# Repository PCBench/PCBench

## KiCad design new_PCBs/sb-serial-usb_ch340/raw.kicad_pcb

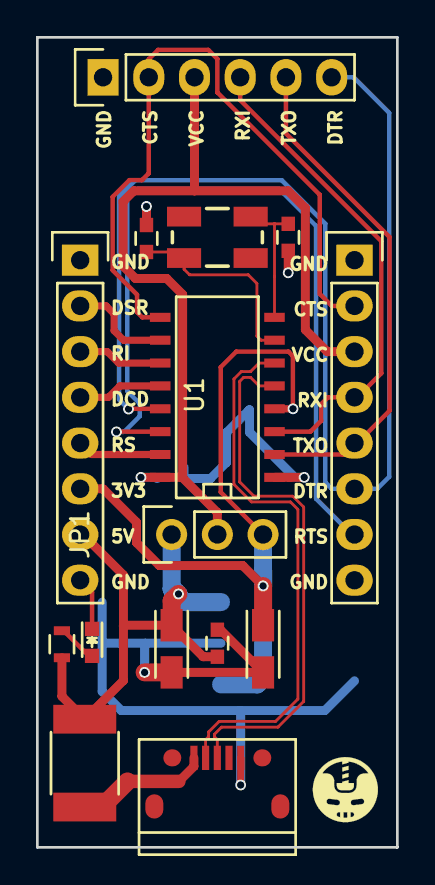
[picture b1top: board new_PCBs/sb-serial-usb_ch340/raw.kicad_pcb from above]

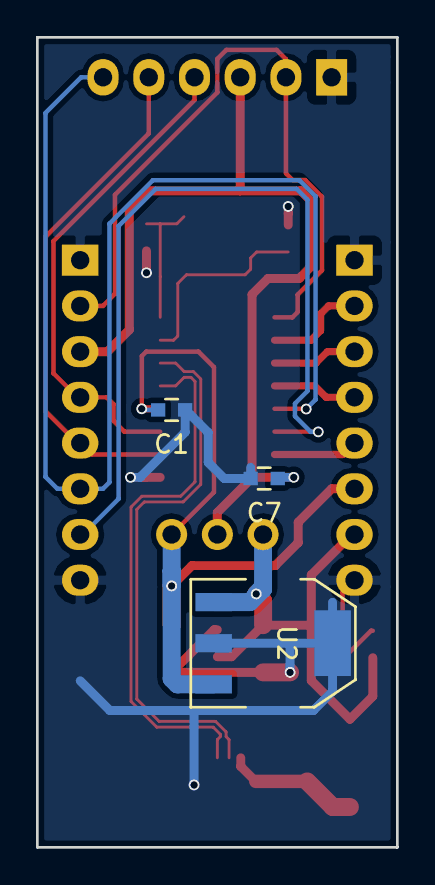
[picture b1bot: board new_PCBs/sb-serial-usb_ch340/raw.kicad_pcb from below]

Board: 2 copper layers, 20.0 x 45.0 mm, 18 parts (3 on the bottom side), 19 nets.

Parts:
C1: 10n; C_0603
C2, C3: 22p; C_0603
C4, C6: 10u 6V TANT; TantalC_SizeA_EIA-3216_Reflow
C5: 1u; C_0603
C7: 100n; C_0603
D1: BLUE; LED_0603
F1: 1.5A; R_1812
JP1: JUMPER3; Pin_Header_Straight_1x03
P1: CONN_01X06; Pin_Header_Straight_1x06
P2, P3: CONN_01X08; Pin_Header_Straight_1x08
P4: MINI-USB; USB_Micro-B
R1: 1K; R_0603
U1: CH340G; SO-16-N
U2: LDO MIC39100 3.3V; SOT-223
Y1: 12Mhz; CRYSTAL-SMD-5X3

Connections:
+5V: C4.1, C5.1, F1.2, JP1.1, P3.7, R1.2, U2.1
CTS: P1.2, P2.2, U1.9
D+: P4.3, U1.5
D-: P4.2, U1.6
DCD: P3.4, U1.12
DSR: P3.2, U1.10
DTR: P1.6, P2.6, U1.13
GND: C1.1, C2.2, C3.2, C4.2, C5.2, C6.2, C7.2, D1.1, P1.1, P2.1, P2.8, P3.1, P3.8, P4.5, U1.1, U2.2, U2.4
unnamed: C2.1, U1.7, Y1.1
unnamed: C3.1, U1.8, Y1.2
unnamed: D1.2, R1.1
unnamed: F1.1, P4.1
RI: P3.3, U1.11
RS232: P3.5, U1.15
RTS: P2.7, U1.14
RXI: P1.4, P2.4, U1.3
TXO: P1.5, P2.5, U1.2
V3: C1.2, C6.1, JP1.3, P3.6, U1.4, U2.3
VCC: C7.1, JP1.2, P1.3, P2.3, U1.16

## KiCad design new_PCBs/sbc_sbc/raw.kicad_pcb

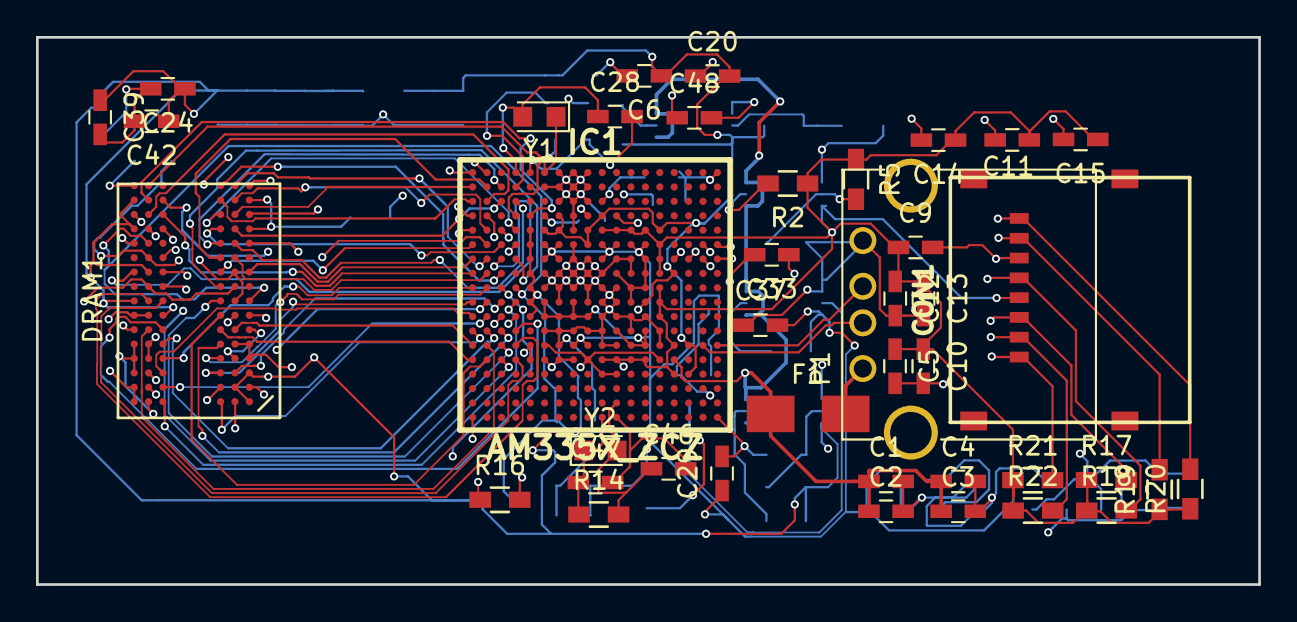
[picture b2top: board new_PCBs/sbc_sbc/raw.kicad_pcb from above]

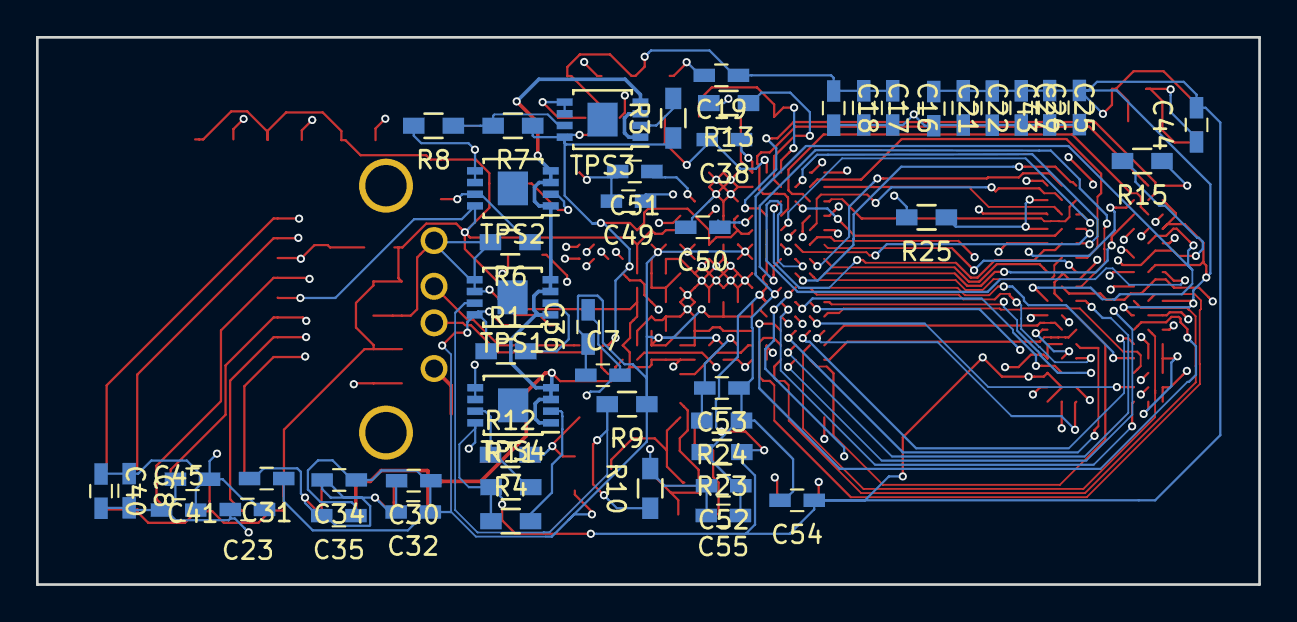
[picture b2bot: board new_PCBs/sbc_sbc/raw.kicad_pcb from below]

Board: 4 copper layers, 67.9 x 30.4 mm, 91 parts (50 on the bottom side), 85 nets.

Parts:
C1, C2, C3, C4, C15, C20, C26, C27, C37, C44, C45: 10uF; C_0603_HandSoldering
C5, C6, C7, C8: 22uF; C_0603_HandSoldering
C9, C10, C11, C12, C13, C14, C16, C17, C18, C19, C29, C30, C31, C32, C33, C34, C35, C36: 10nF; C_0603_HandSoldering
C21, C22, C23, C24, C25, C39, C40, C41, C42, C43, C48, C49, C50, C51: 1uF; C_0603_HandSoldering
C28, C38: 25pF; C_0603_HandSoldering
C46, C47: 24pF; C_0603_HandSoldering
C52, C53, C54, C55: 0.1uF; C_0603_HandSoldering
CON1: Micro_SD_Card; MICRO_SD_HINGE_AMP
DRAM1: DRAM-IS43TR16128B-125KBL; BGA-96_pitch0.8mm_dia0.4mm
F1: Polyfuse; Fuse_SMD1206_HandSoldering
IC1: AM335X_ZCZ; bga-csg324
P1: USB_A
R1, R2, R3, R4: 499K; R_0603_HandSoldering
R5: 250K; R_0603_HandSoldering
R6, R8, R10, R12: 80K; R_0603_HandSoldering
R7: 100K; R_0603_HandSoldering
R9: 30K; R_0603_HandSoldering
R11: 70K; R_0603_HandSoldering
R13, R17, R18, R19, R20, R21, R22, R25: 10K; R_0603_HandSoldering
R14: 1M; R_0603_HandSoldering
R15: 240; R_0603_HandSoldering
R16: 49.9; R_0603_HandSoldering
R23, R24: 1K; R_0603_HandSoldering
TPS1, TPS2, TPS3, TPS4: TPS82084; MSOP-8-1EP_3x3mm_Pitch0.65mm
Y1: 32.768KHz; Crystal_SMD_2012-2pin_2.0x1.2mm_HandSoldering
Y2: 24MHz; Crystal_SMD_2012-2pin_2.0x1.2mm_HandSoldering

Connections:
1.1V: C7.1, C29.1, C30.1, C31.1, C32.1, C33.1, C34.1, C35.1, C36.1, C37.2, IC1.A2, IC1.F6, IC1.F7, IC1.F10, IC1.F11, IC1.F12, IC1.F13, IC1.G6, IC1.G7, IC1.G10, IC1.G13, IC1.H11, IC1.H13, IC1.J12, IC1.J13, IC1.K6, IC1.K8, IC1.K12, IC1.L6, IC1.L7, IC1.L8, IC1.L9, IC1.M11, IC1.M13, IC1.N8, IC1.N9, IC1.N12, IC1.N13, R1.1, R9.1, TPS1.8
1.8V: C6.1, C16.1, C17.1, C18.1, C19.1, C20.2, IC1.D7, IC1.D10, IC1.E6, IC1.E7, IC1.E9, IC1.E14, IC1.F9, IC1.H15, IC1.K13, IC1.N6, IC1.N16, IC1.P9, IC1.P14, IC1.R10, IC1.R11, IC1.R16, R3.1, R7.1, TPS3.8
+1.5V: C8.1, C21.1, C22.1, C23.1, C24.1, C25.1, C26.1, C27.2, C39.1, C40.1, C41.1, C42.1, C43.1, C44.2, C45.2, C54.1, DRAM1.A1, DRAM1.A8, DRAM1.B2, DRAM1.C1, DRAM1.C9, DRAM1.D2, DRAM1.D9, DRAM1.E9, DRAM1.F1, DRAM1.G7, DRAM1.H2, DRAM1.H9, DRAM1.K2, DRAM1.K8, DRAM1.N1, DRAM1.N9, DRAM1.R1, DRAM1.R9, IC1.E5, IC1.F5, IC1.G5, IC1.H5, IC1.J5, IC1.K5, IC1.L5, R4.1, R11.1, R23.1, R25.1, TPS4.8
+3V3: C5.1, C9.1, C10.1, C11.1, C12.1, C13.1, C14.1, C15.1, CON1.4, IC1.E10, IC1.E11, IC1.E12, IC1.E13, IC1.F14, IC1.G14, IC1.H14, IC1.J14, IC1.K14, IC1.L14, IC1.N5, IC1.N15, IC1.P5, IC1.P6, IC1.P7, IC1.P8, IC1.P10, IC1.P11, IC1.P12, IC1.P13, IC1.R15, R2.1, R5.1, R17.1, R18.1, R19.1, R20.1, R21.1, R22.1, TPS2.8
+5V: C1.1, C2.1, C3.1, C4.1, F1.1, IC1.P15, TPS1.1, TPS1.3, TPS1.4, TPS2.1, TPS2.3, TPS2.4, TPS3.1, TPS3.3, TPS3.4, TPS4.1, TPS4.3, TPS4.4
/1.1FB: R9.2, R10.1, TPS1.7
/1.5FB: R11.2, R12.1, TPS4.7
/1.8FB: R7.2, R8.1, TPS3.7
/3.3FB: R5.2, R6.1, TPS2.7
/DDR_A0: DRAM1.N3, IC1.F3
/DDR_A1: DRAM1.P7, IC1.H1
/DDR_A2: DRAM1.P3, IC1.E4
/DDR_A3: DRAM1.N2, IC1.C3
/DDR_A4: DRAM1.P8, IC1.C2
/DDR_A5: DRAM1.P2, IC1.B1
/DDR_A6: DRAM1.R8, IC1.D5
/DDR_A7: DRAM1.R2, IC1.E2
/DDR_A8: DRAM1.T8, IC1.D4
/DDR_A9: DRAM1.R3, IC1.C1
/DDR_A10: DRAM1.L7, IC1.F4
/DDR_A11: DRAM1.R7, IC1.F2
/DDR_A12: DRAM1.N7, IC1.E3
/DDR_A13: DRAM1.T3, IC1.H3
/DDR_BA0: DRAM1.M2, IC1.C4
/DDR_BA1: DRAM1.N8, IC1.E1
/DDR_BA2: DRAM1.M3, IC1.B3
/DDR_CASn: DRAM1.K3, IC1.F1
/DDR_CK: DRAM1.J7, IC1.D2
/DDR_CKE: DRAM1.K9, IC1.G3
/DDR_CKn: DRAM1.K7, IC1.D1
/DDR_CSn0: DRAM1.L2, IC1.H2
/DDR_D0: DRAM1.E3, IC1.M3
/DDR_D1: DRAM1.F7, IC1.M4
/DDR_D2: DRAM1.F2, IC1.N1
/DDR_D3: DRAM1.F8, IC1.N2
/DDR_D4: DRAM1.H3, IC1.N3
/DDR_D5: DRAM1.H8, IC1.N4
/DDR_D6: DRAM1.G2, IC1.P3
/DDR_D7: DRAM1.H7, IC1.P4
/DDR_D8: DRAM1.D7, IC1.J1
/DDR_D9: DRAM1.C3, IC1.K1
/DDR_D10: DRAM1.C8, IC1.K2
/DDR_D11: DRAM1.C2, IC1.K3
/DDR_D12: DRAM1.A7, IC1.K4
/DDR_D13: DRAM1.A2, IC1.L3
/DDR_D14: DRAM1.B8, IC1.L4
/DDR_D15: DRAM1.A3, IC1.M1
/DDR_DQM0: DRAM1.E7, IC1.M2
/DDR_DQM1: DRAM1.D3, IC1.J2
/DDR_DQS0: DRAM1.F3, IC1.P1
/DDR_DQS1: DRAM1.C7, IC1.L1
/DDR_DQSn0: DRAM1.G3, IC1.P2
/DDR_DQSn1: DRAM1.B7, IC1.L2
/DDR_ODT: DRAM1.K1, IC1.G1
/DDR_RASn: DRAM1.J3, IC1.G4
/DDR_RESETn: DRAM1.T2, IC1.G2, R25.2
/DDR_VREF: C52.1, C53.1, C54.2, C55.1, DRAM1.H1, DRAM1.M8, IC1.J4, R23.2, R24.1
/DDR_WEn: DRAM1.L3, IC1.B2
/DDR_ZQ: DRAM1.L8, R15.2
/MMC0_CLK: CON1.5, IC1.G17, R18.2
/MMC0_CMD: CON1.3, IC1.G18, R17.2
/MMC0_DAT0: CON1.7, IC1.G16, R19.2
/MMC0_DAT1: CON1.8, IC1.G15, R20.2
/MMC0_DAT2: CON1.1, IC1.F18, R21.2
/MMC0_DAT3: CON1.2, IC1.F17, R22.2
/USBD+: IC1.N17, P1.2
/USBD-: IC1.N18, P1.3
GND: C1.2, C2.2, C3.2, C4.2, C5.2, C6.2, C7.2, C8.2, C9.2, C10.2, C11.2, C12.2, C13.2, C14.2, C15.2, C16.2, C17.2, C18.2, C19.2, C20.1, C21.2, C22.2, C23.2, C24.2, C25.2, C26.2, C27.1, C29.2, C30.2, C31.2, C32.2, C33.2, C34.2, C35.2, C36.2, C37.1, C39.2, C40.2, C41.2, C42.2, C43.2, C44.1, C45.1, C48.2, C49.2, C50.2, C51.2, C52.2, C53.2, C55.2, CON1.6, DRAM1.A9, DRAM1.B1, DRAM1.B3, DRAM1.B9, DRAM1.D1, DRAM1.D8, DRAM1.E1, DRAM1.E2, DRAM1.E8, DRAM1.F9, DRAM1.G1, DRAM1.G8, DRAM1.G9, DRAM1.J2, DRAM1.J8, DRAM1.M1, DRAM1.M9, DRAM1.P1, DRAM1.P9, DRAM1.T1, DRAM1.T9, IC1.A1, IC1.A7, IC1.A8, IC1.A9, IC1.A18, IC1.B6, IC1.B7, IC1.B8, IC1.B9, IC1.C7, IC1.C8, IC1.C9, IC1.D8, IC1.E8, IC1.F8, IC1.G8, IC1.G9, IC1.G11, IC1.G12, IC1.H6, IC1.H7, IC1.H8, IC1.H9, IC1.H10, IC1.H12, IC1.J6, IC1.J7, IC1.J8, IC1.J9, IC1.J10, IC1.J11, IC1.K7, IC1.K9, IC1.K10, IC1.K11, IC1.L10, IC1.L11, IC1.L12, IC1.L13, IC1.M6, IC1.M7, IC1.M8, IC1.M9, IC1.M10, IC1.M12, IC1.M14, IC1.N7, IC1.N10, IC1.N11, IC1.N14, IC1.V1, IC1.V18, P1.4, R6.2, R8.2, R10.2, R12.2, R13.2, R15.1, R16.2, R24.2, TPS1.5, TPS1.6, TPS2.5, TPS2.6, TPS3.5, TPS3.6, TPS4.5, TPS4.6
GND_OSC0: C46.2, C47.2, IC1.V11
GND_OSC1: C28.2, C38.2, IC1.A5
unnamed: C28.1, IC1.A4, Y1.2
unnamed: C38.1, IC1.A6, Y1.1
unnamed: C46.1, IC1.U11, R14.2, Y2.2
unnamed: C47.1, IC1.V10, R14.1, Y2.1
unnamed: C48.1, IC1.D11
unnamed: C49.1, IC1.D9
unnamed: C50.1, IC1.D6
unnamed: C51.1, IC1.C10
unnamed: F1.2, P1.1
unnamed: IC1.B4, R13.1
unnamed: IC1.J3, R16.1
unnamed: R1.2, TPS1.2
unnamed: R2.2, TPS2.2
unnamed: R3.2, TPS3.2
unnamed: R4.2, TPS4.2

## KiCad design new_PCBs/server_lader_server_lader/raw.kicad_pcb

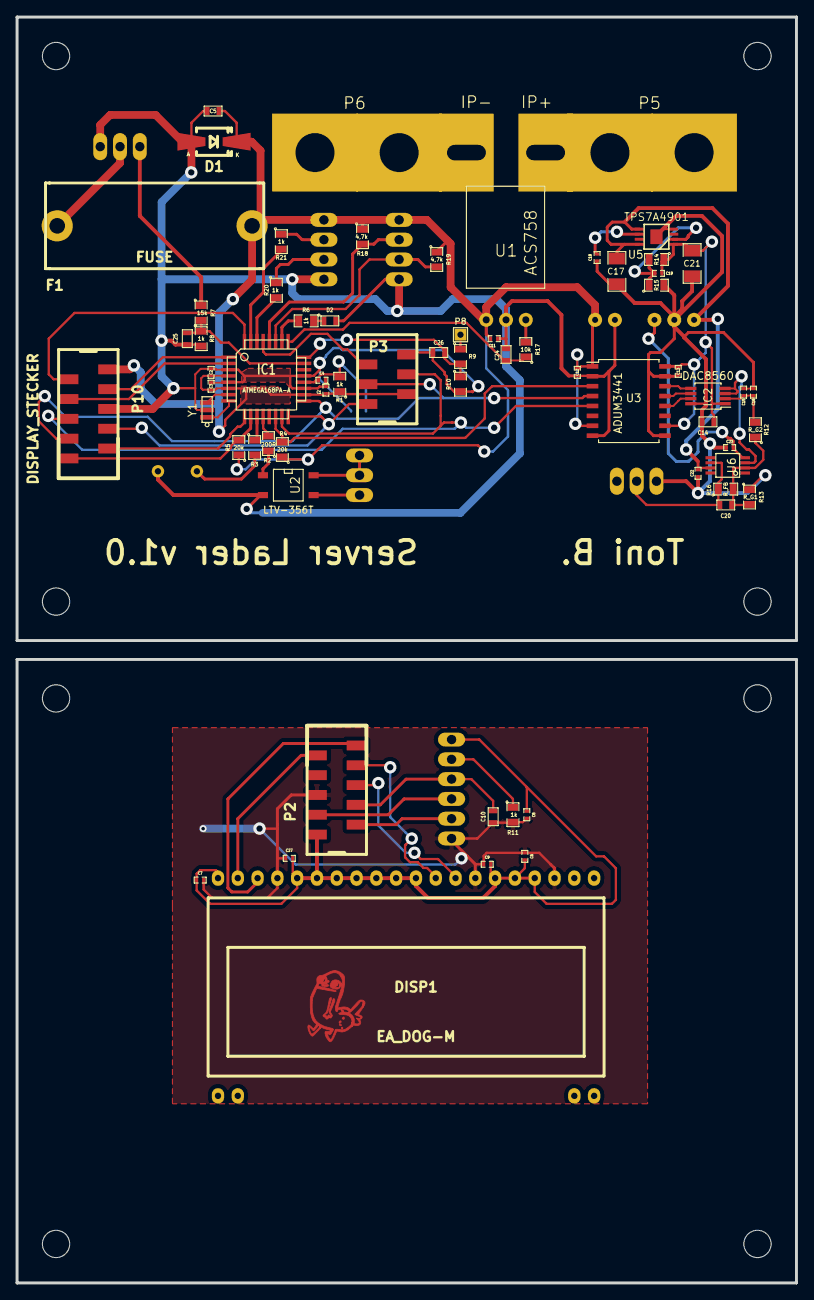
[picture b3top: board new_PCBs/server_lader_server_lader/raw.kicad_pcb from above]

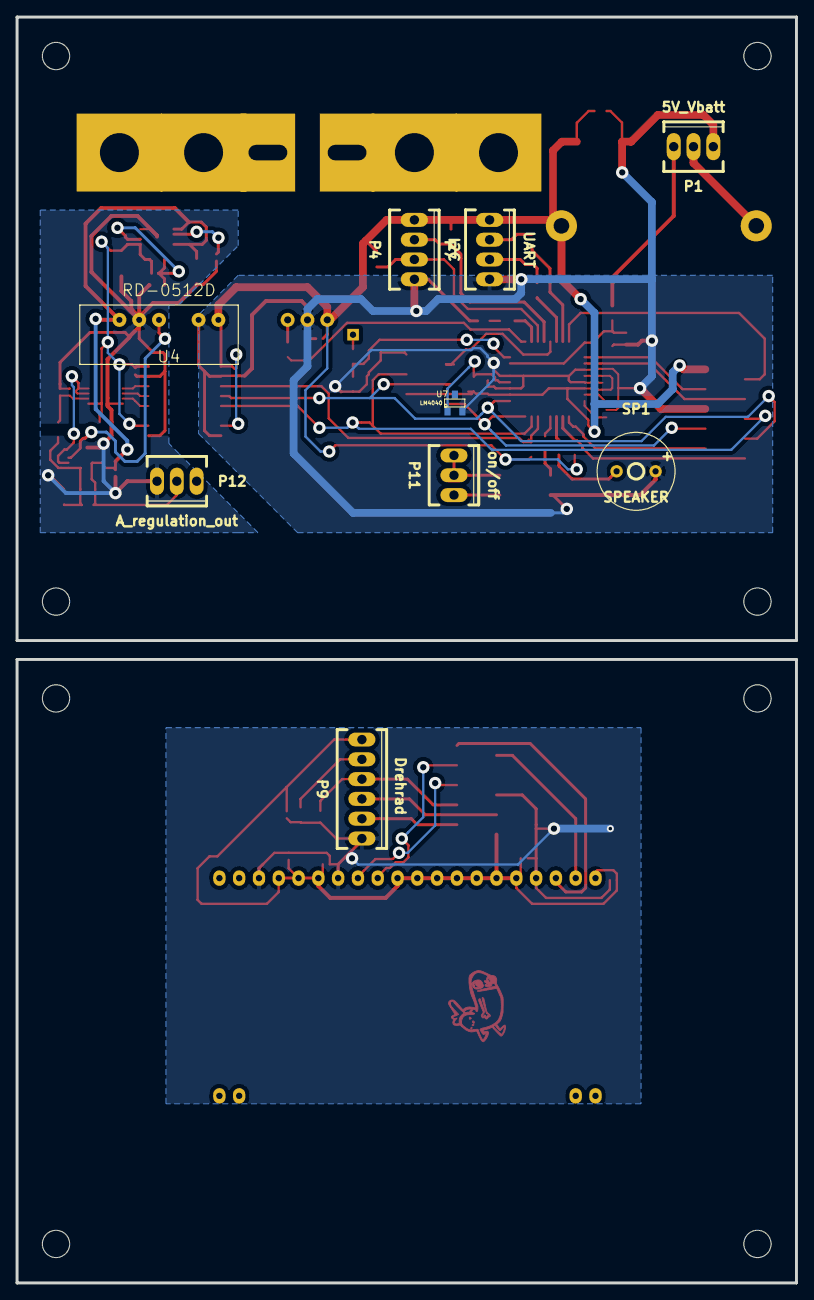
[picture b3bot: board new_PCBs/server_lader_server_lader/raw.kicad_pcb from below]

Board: 2 copper layers, 100.0 x 162.4 mm, 77 parts (9 on the bottom side), 59 nets.

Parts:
C1, C2, C3, C4, C6, C7, C8, C9, C11, C12, C13, C15, C16, C22, C23, C27: 100nF; SMD-0402
C5, C10, C14, C24: 1uF; SMD-0603
C17, C21: 10uF; SMD-1206
C18, C19: 10nF; SMD-0402
C20: C_comp; SMD-0603
C25: 100nF; SMD-0603
C26: C; SMD-0603
D1: ZENER 5,6V; Diode-Universal-SMA-SMB_Handsoldering
D2: LED; SMD-0603
DISP1: EA_DOG-M; EA_DOG-M_DISP
F1: FUSE; fuse_holder_Schurther
IC1: ATMEGA168PA-A; TQFP-32
IC2: DAC8560; MSOP-8_3x3mm_Pitch0.65mm
Outl: EuroBoard_halb_Type-I_100mmX80mm_holes
Outl#2: EuroBoard_halb_Type-I_100mmX80mm_holes
P1: 5V_Vbatt; Socket_MOLEX-KK-RM2-54mm_Lock_3pin_straight
P2, P10: DISPLAY_STECKER; micro_match5x2
P3: CONN_02X03; micro_match3x2
P4: I2C; Socket_MOLEX-KK-RM2-54mm_Lock_4pin_straight
P5: IP+; power_terminal
P6: IP-; power_terminal
P7: UART; Socket_MOLEX-KK-RM2-54mm_Lock_4pin_straight
P8: CONN_01X01; SIL-1
P9: Drehrad; Socket_MOLEX-KK-RM2-54mm_Lock_6pin_straight
P11: on/off; Socket_MOLEX-KK-RM2-54mm_Lock_3pin_straight
P12: A_regulation_out; Socket_MOLEX-KK-RM2-54mm_Lock_3pin_straight
R1, R6, R8, R11, R20, R21: 1k; SMD-0805
R2: 200R; SMD-0805
R3, R9, R10: R; SMD-0805
R4, R5: 20k; SMD-0805
R7: 15k; SMD-0805
R12: R_G2; SMD-0805
R13: R_G1; SMD-0805
R14: 33k; SMD-0805
R15, R17: 10k; SMD-0805
R16: R_FB; SMD-0805
R18, R19: 4,7k; SMD-0805
SP1: SPEAKER; Buzzer_AI-1027-TWT-5V-R
U1: ACS758; ACS758_PFF
U2: LTV-356T; SO-4
U3: ADUM3441; SOIC-16_7.5x10.3mm_Pitch1.27mm
U4: RD-0512D; RD-xx12D
U5: TPS7A4901; MSOP-8_power_pad
U6: OPA827; SSOP-8
U7: LM4040; SOT-23
Y1: RESONATEUR; CerOsc_3,2x1,3

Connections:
+5VA: C13.1, C14.1, C19.1, C21.1, IC2.1, R14.1, U3.10, U3.16, U5.1
+12V: C17.1, C22.1, U4.6, U5.5, U5.8, U6.7
-12V: C23.2, U4.4, U6.4
/A: IC1.32, P10.2
/A_D: P2.2, P9.2
/B: IC1.1, P10.3
/B_D: P2.3, P9.3
/CSB: IC1.10, P10.10, R5.2
/CSB_D: DISP1.38, P2.10
/MISO: IC1.16, P3.1, P10.7
/MOSI: IC1.15, P3.4, P10.6, U3.5
/MOSI_D: DISP1.28, P2.6
/RS: IC1.9, P10.9
/RST: IC1.29, P3.5
/RS_D: DISP1.39, P2.9
/S: IC1.2, P10.4
/SCK: IC1.17, P3.3, P10.8, U3.4
/SCK_D: DISP1.29, P2.8
/SCL: IC1.28, P4.3, R18.2
/SDA: IC1.27, P4.2, R19.2
/SS_DAC: IC1.14, R4.2, U3.3
/S_D: C10.1, P2.4, P9.4
/U_Netzteil: C25.1, IC1.23, R7.2, R8.1
/U_Strom: C24.1, IC1.25, R17.1
/U_reserve: C26.1, IC1.24, R9.2, R10.1
/V_current: C20.1, P12.2, R16.1, U6.6
/Vref: C15.1, C16.1, IC2.2, R12.2
/on: R2.1, U2.1
AGND: C13.2, C14.2, C15.2, C16.2, C17.2, C18.2, C21.2, C22.2, C23.1, IC2.8, P12.1, R13.1, R15.2, U3.9, U3.15, U4.5, U5.4, U5.9
GND: C1.2, C2.2, C3.2, C4.2, C5.2, C6.2, C7.2, C8.2, C9.2, C10.2, C11.2, C12.2, C24.2, C25.2, C26.2, C27.2, D1.1, D2.2, DISP1.23, DISP1.27, DISP1.37, IC1.3, IC1.5, IC1.19, IC1.21, P1.1, P2.5, P3.6, P4.1, P7.1, P9.1, P10.5, R8.2, R10.2, R11.2, SP1.2, U1.2, U2.2, U3.2, U3.8, U4.2, U7.2, Y1.2
unnamed: C4.1, IC1.20, R1.2, U7.1
unnamed: C18.1, U5.6
unnamed: C19.2, R14.2, R15.1, U5.2
unnamed: C20.2, R12.1, R13.2, R16.2, U6.2
unnamed: D2.1, R6.1
unnamed: F1.1, P1.2
unnamed: IC1.7, Y1.3
unnamed: IC1.8, Y1.1
unnamed: IC1.11, R3.1
unnamed: IC1.12, R2.2
unnamed: IC1.26, R6.2
unnamed: IC1.30, R20.2
unnamed: IC1.31, R21.2
unnamed: IC2.3, IC2.4, U6.3
unnamed: IC2.5, U3.14
unnamed: IC2.6, U3.13
unnamed: IC2.7, U3.12
unnamed: P1.3, R7.1
unnamed: P5.1, U1.4
unnamed: P6.1, U1.5
unnamed: P7.2, R20.1
unnamed: P7.3, R21.1
unnamed: P8.1, R9.1
unnamed: P9.5, R11.1
unnamed: P11.1, U2.3
unnamed: P11.2, P11.3, U2.4
unnamed: R3.2, SP1.1
unnamed: R17.2, U1.3
VCC: C1.1, C2.1, C3.1, C5.1, C6.1, C7.1, C8.1, C9.1, C11.1, C12.1, C27.1, D1.2, DISP1.24, DISP1.25, DISP1.26, DISP1.30, DISP1.31, DISP1.32, DISP1.33, DISP1.34, DISP1.35, DISP1.36, DISP1.40, F1.2, IC1.4, IC1.6, IC1.18, P2.1, P3.2, P4.4, P7.4, P9.6, P10.1, R1.1, R4.1, R5.1, R18.1, R19.1, U1.1, U3.1, U3.7, U4.1

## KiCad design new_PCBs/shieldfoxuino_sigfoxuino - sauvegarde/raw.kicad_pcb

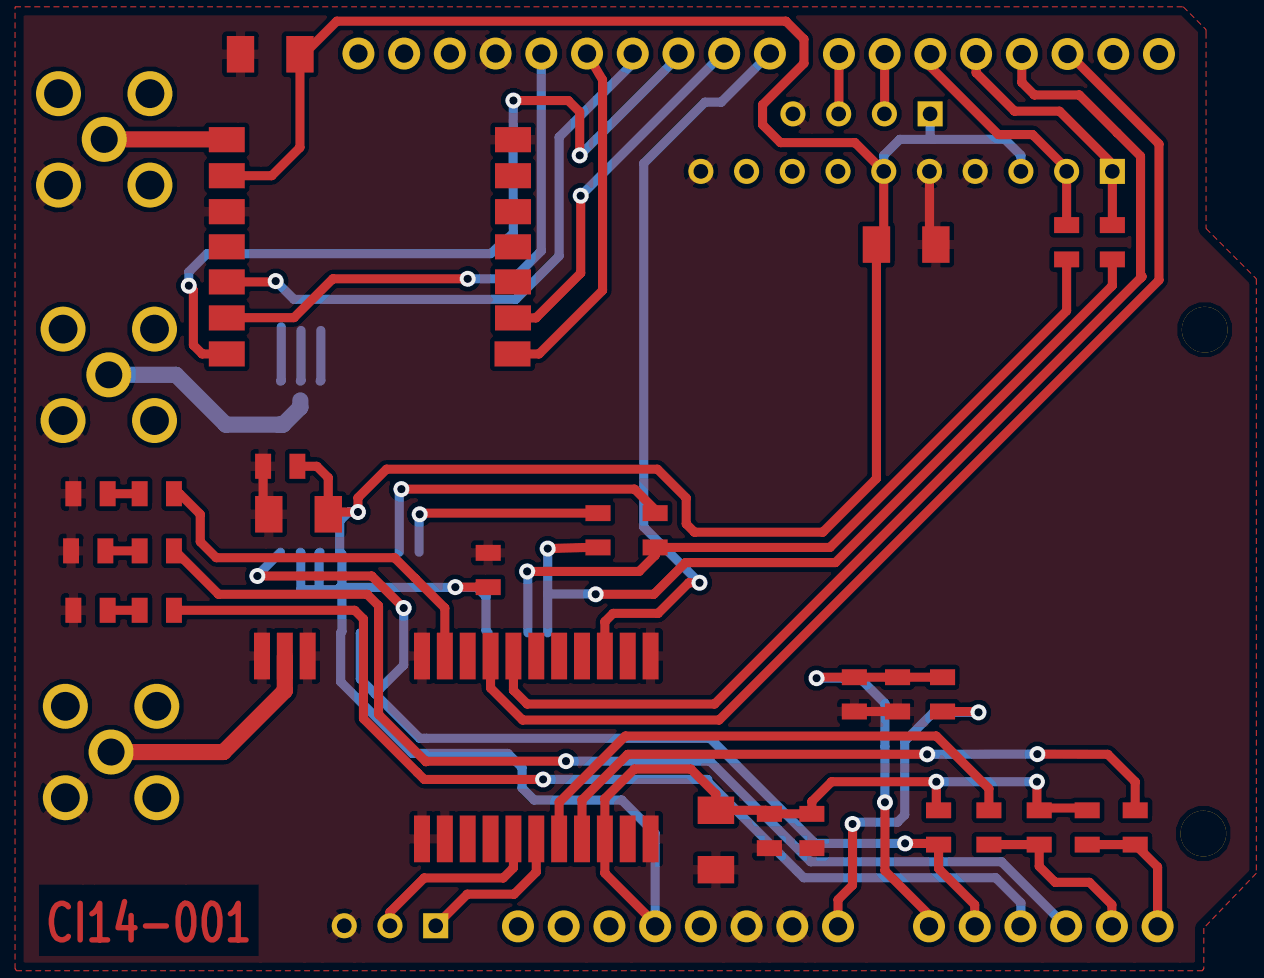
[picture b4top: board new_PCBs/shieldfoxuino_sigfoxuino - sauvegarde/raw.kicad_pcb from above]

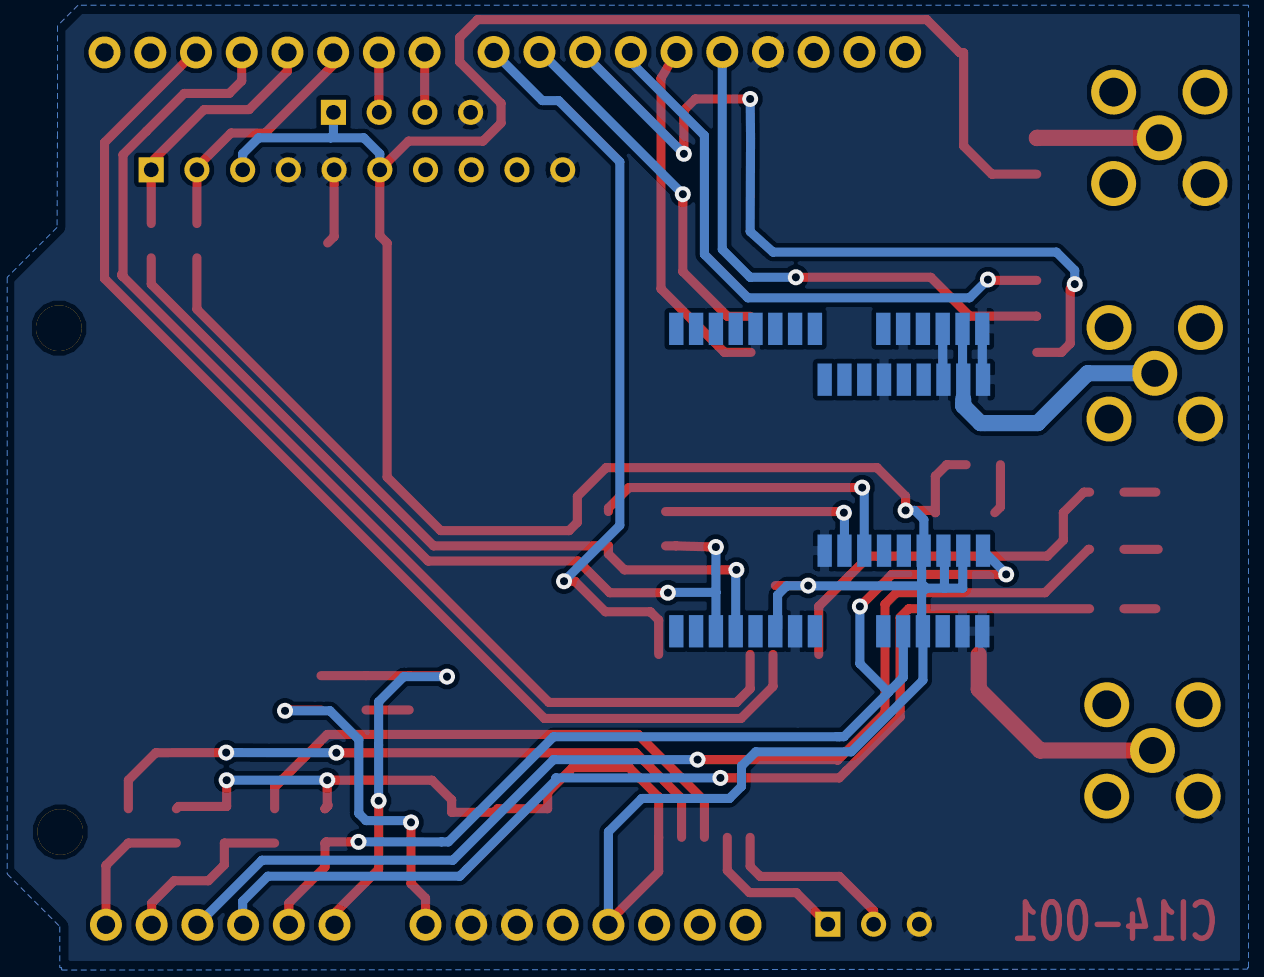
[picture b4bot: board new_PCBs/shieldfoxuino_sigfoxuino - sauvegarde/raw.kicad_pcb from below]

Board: 2 copper layers, 42 parts (2 on the bottom side), 36 nets.

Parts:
C1, C4, C6, C8: 0.1uF; SM0805
C2, C5, C7: 10uF/9V; SM1206
C3: 10pF; SM0805
C9: 1uF/9V; SM1206
CON6_1: CONN_6; Con6
CON8_1, CON8_2: CONN_8; Con8
CON10_1: CONN_10; Con10
D1, D2, D3: LED GREEN; SM0805
J1, J2, J3: SMA_TH; SMA-SMB_right_angle
J4: SIL10; SIL-10
K1: CONN_3; SIL-3
P1: CONN_4; SIL-4
R1, R2: 0R0; SM0805
R3, R4: 4K7; SM0805
R5: 47K; SM0805
R6, R7, R15: 220R; SM0805
R8, R9, R10, R11: 0R; SM0805
R12: 10K; SM0805
R13: 1K; SM0805
U1: LEA-7X; LEA-xx
U2: MAX-7X; MAX-xx
U3: RFM12
U4: TD1202
V4, V5: 1pin

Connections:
+3.3V: C1.1, C2.1, C3.1, C4.1, C5.1, C6.1, C7.1, C9.1, CON8_1.4, J4.3, J4.6, P1.1, R3.2, R4.2, R5.1, U1.6, U1.11, U2.6, U2.7, U2.8, U3.9, U4.9
/PB0: CON10_1.1, U4.14
/PB1: CON10_1.2, U3.2
/PB2: CON10_1.3, U3.14
/PB3: CON10_1.4, U3.12
/PB4: CON10_1.5, U3.1
/PB5: CON10_1.6, U3.13
/PC0: C8.1, CON6_1.1, R12.2, R13.1
/PC1: CON6_1.2, R5.2, U1.10, U2.9
/PC2: CON6_1.3, R7.1
/PC3: CON6_1.4, R6.1
/PD2: CON8_2.3, U4.19
/PD3: CON8_2.4, U4.18
/PD4: CON8_2.5, J4.1, R8.2
/PD5: CON8_2.6, J4.2, R9.2
/PD6: CON8_2.7, P1.2
/PD7: CON8_2.8, P1.3
/RF_GPS: J1.1, U1.16, U2.11
/RF_RF12: J2.1, U3.8
/RF_SIG: J3.1, U4.24
/RX_SFT: R8.1, R11.1, U1.3
/SCL: CON6_1.6, CON10_1.10, R2.1, R4.1
/SDA: CON6_1.5, CON10_1.9, R1.1, R3.1
/STATUS_SIG: R15.1, U4.21
/TX_SFT: R9.1, R10.1, U1.4
/VIN: CON8_1.8, R12.1
GND: C1.2, C2.2, C3.2, C4.2, C5.2, C6.2, C7.2, C8.2, C9.2, CON8_1.6, CON8_1.7, CON10_1.7, D1.2, D2.2, D3.2, J1.2, J2.2, J3.2, J4.4, J4.5, J4.10, K1.3, P1.4, R13.2, U1.7, U1.13, U1.14, U1.15, U1.17, U1.19, U1.24, U2.1, U2.10, U2.12, U2.15, U3.7, U3.10, U4.1, U4.2, U4.11, U4.12, U4.22, U4.23, U4.25
unnamed: R2.2, U4.8
unnamed: K1.2, U4.5
unnamed: K1.1, U4.6
unnamed: R11.2, U2.2
unnamed: R10.2, U2.3
unnamed: R1.2, U4.7
unnamed: D2.1, R7.2
unnamed: D1.1, R6.2
unnamed: D3.1, R15.2

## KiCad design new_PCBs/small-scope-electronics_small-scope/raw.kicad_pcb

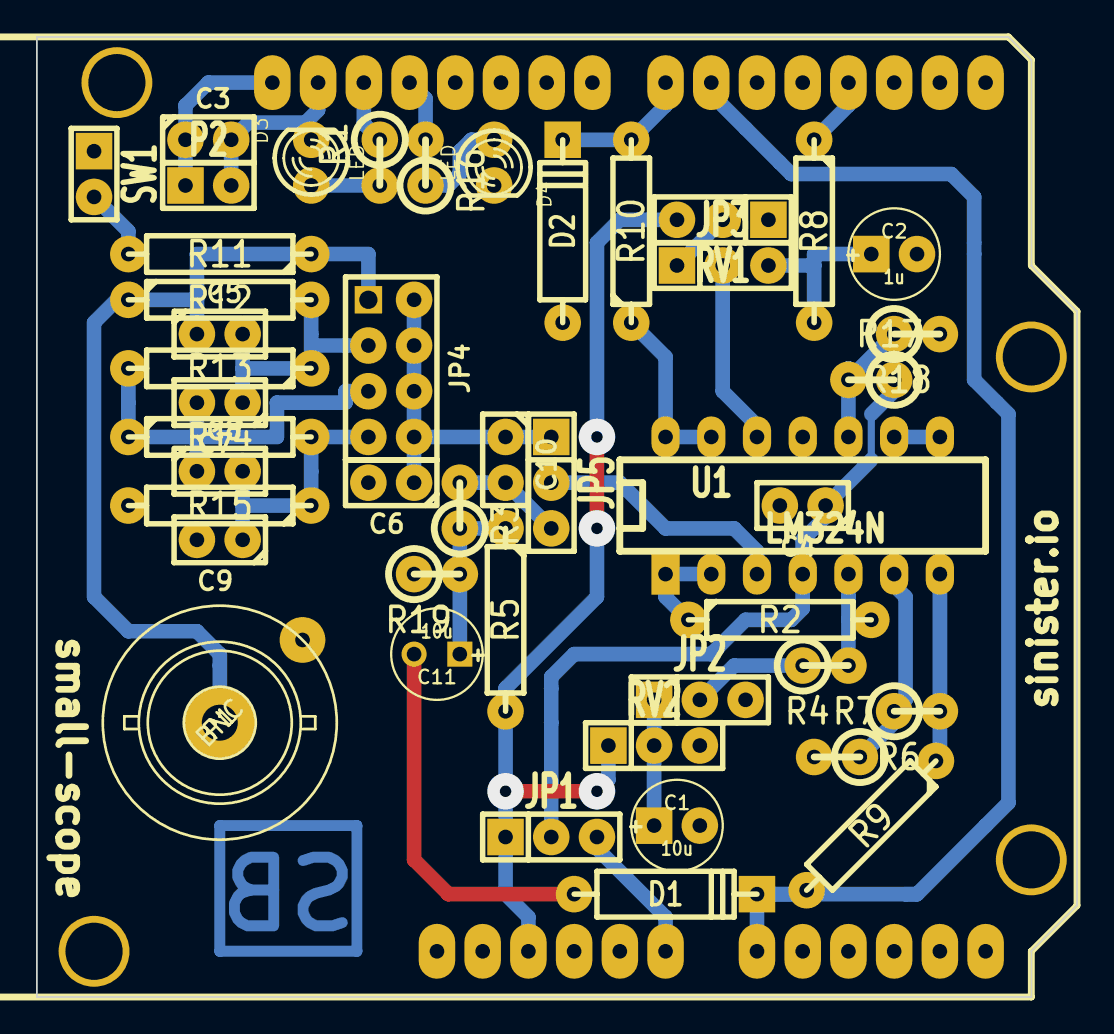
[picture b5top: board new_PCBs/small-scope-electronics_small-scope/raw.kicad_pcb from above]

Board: 2 copper layers, 57.8 x 53.3 mm, 46 parts (0 on the bottom side), 33 nets.

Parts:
C1, C11: 10u; C1V5
C2: 1u; C1V5
C3, C4: 1n; C1
C5: 16p; C1
C6: 10p; C1
C7: 130p; C1
C8, C9: 270p; C1
C10: 10u/35V; C1
D1, D2: 5.1V; D4
D3, D4: LED; LED-3MM
JP1: VDD SRC; SIL-3
JP2: DC BIAS; SIL-3
JP3: THR SRC; SIL-3
JP4: ATT SEL; pin_array_4x2
JP5: AC/DC; SIL-3
P1: BNC; BNCv
P2: AREF; SIL-2
R1, R16: 220; R1
R2, R5: 10k; R4-LARGE_PADS
R3, R4, R6, R7, R17, R18, R19: 10k; R1
R8: 1k8; R4-LARGE_PADS
R9, R10: 220; R4-LARGE_PADS
R11: 50; R4-LARGE_PADS
R12: 800k; R4-LARGE_PADS
R13: 100k; R4-LARGE_PADS
R14, R15: 50k; R4-LARGE_PADS
RV1, RV2: 10k; SIL-3
SHIELD1: ARDUINO_SHIELD
SW1: STAT DIS; SIL-2
U1: LM324N; DIP-14__300_ELL

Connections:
/2.5V: C11.1, R3.1, R5.1, R19.2
/BIAS: C1.1, JP2.1, RV2.2
/ERR_LED: R1.1, SHIELD1.13
/INFO_LED: R16.2, SHIELD1.12
/SIG_ACDC: JP5.2, U1.3
/SIG_ATT: C6.1, C10.1, JP4.2, JP4.4, JP4.6, JP4.8, JP5.1
/SIG_IN: C5.1, JP4.1, P1.1, R11.1, R12.1
/SIG_UC: D1.2, R9.2, SHIELD1.6, SHIELD1.AD0
/THR_IN: D2.2, R10.2, SHIELD1.7
/THR_OUT: R8.1, SHIELD1.3
/Vin: JP1.3, SHIELD1.V_IN
/x5: C5.2, C7.1, JP4.3, R12.2, R13.1
/x10: C7.2, C8.1, JP4.5, R13.2, R14.1
/x20: C8.2, C9.1, JP4.7, R14.2, R15.1
GND: C1.2, C2.2, C3.2, C4.2, C6.2, C9.2, C11.2, D1.1, D2.1, D3.2, D4.2, JP2.3, P1.2, P2.2, R7.2, R15.2, R18.2, R19.1, RV1.1, RV2.3, SHIELD1.GND1, SHIELD1.GND2, SHIELD1.GND3, SW1.1, U1.11
unnamed: R11.2, SW1.2
unnamed: JP3.2, U1.12
unnamed: JP3.1, RV1.2
unnamed: R2.1, U1.1, U1.2
unnamed: R2.2, R4.2, U1.5
unnamed: R6.1, R7.1, U1.6
unnamed: R6.2, R9.1, U1.7
unnamed: R10.1, U1.13, U1.14
unnamed: JP2.2, R4.1
unnamed: C3.1, P2.1, SHIELD1.AREF
unnamed: C10.2, JP5.3, R3.2
unnamed: R17.2, R18.1, U1.10
unnamed: D3.1, R1.2
unnamed: U1.8, U1.9
unnamed: D4.1, R16.1
unnamed: C2.1, JP3.3, R8.2
VCC: JP1.1, R5.2, RV1.3, RV2.1, SHIELD1.5V
VDD: C4.1, JP1.2, R17.1, U1.4
